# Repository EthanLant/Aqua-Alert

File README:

# Project Start: 01/12/26
# Contributors:
#   Finn Kramer
#   Ethan Lant
#   Braedyn Thompson
#   Damen Visscher
# Project:
#   Aqua Alert
# Contains:
#   Code for the Lifeguard System
#       - Information Processing, Water Sensor Compatability and Integration, Bluetooth Operation, Antenna Operation
#   Code for the Manager System
#       - Information Processing, LCD Operation and UI, Bluetooth Information Reception, Alert Operation (Yet to be Fully Determined)
#   Future PCB Design

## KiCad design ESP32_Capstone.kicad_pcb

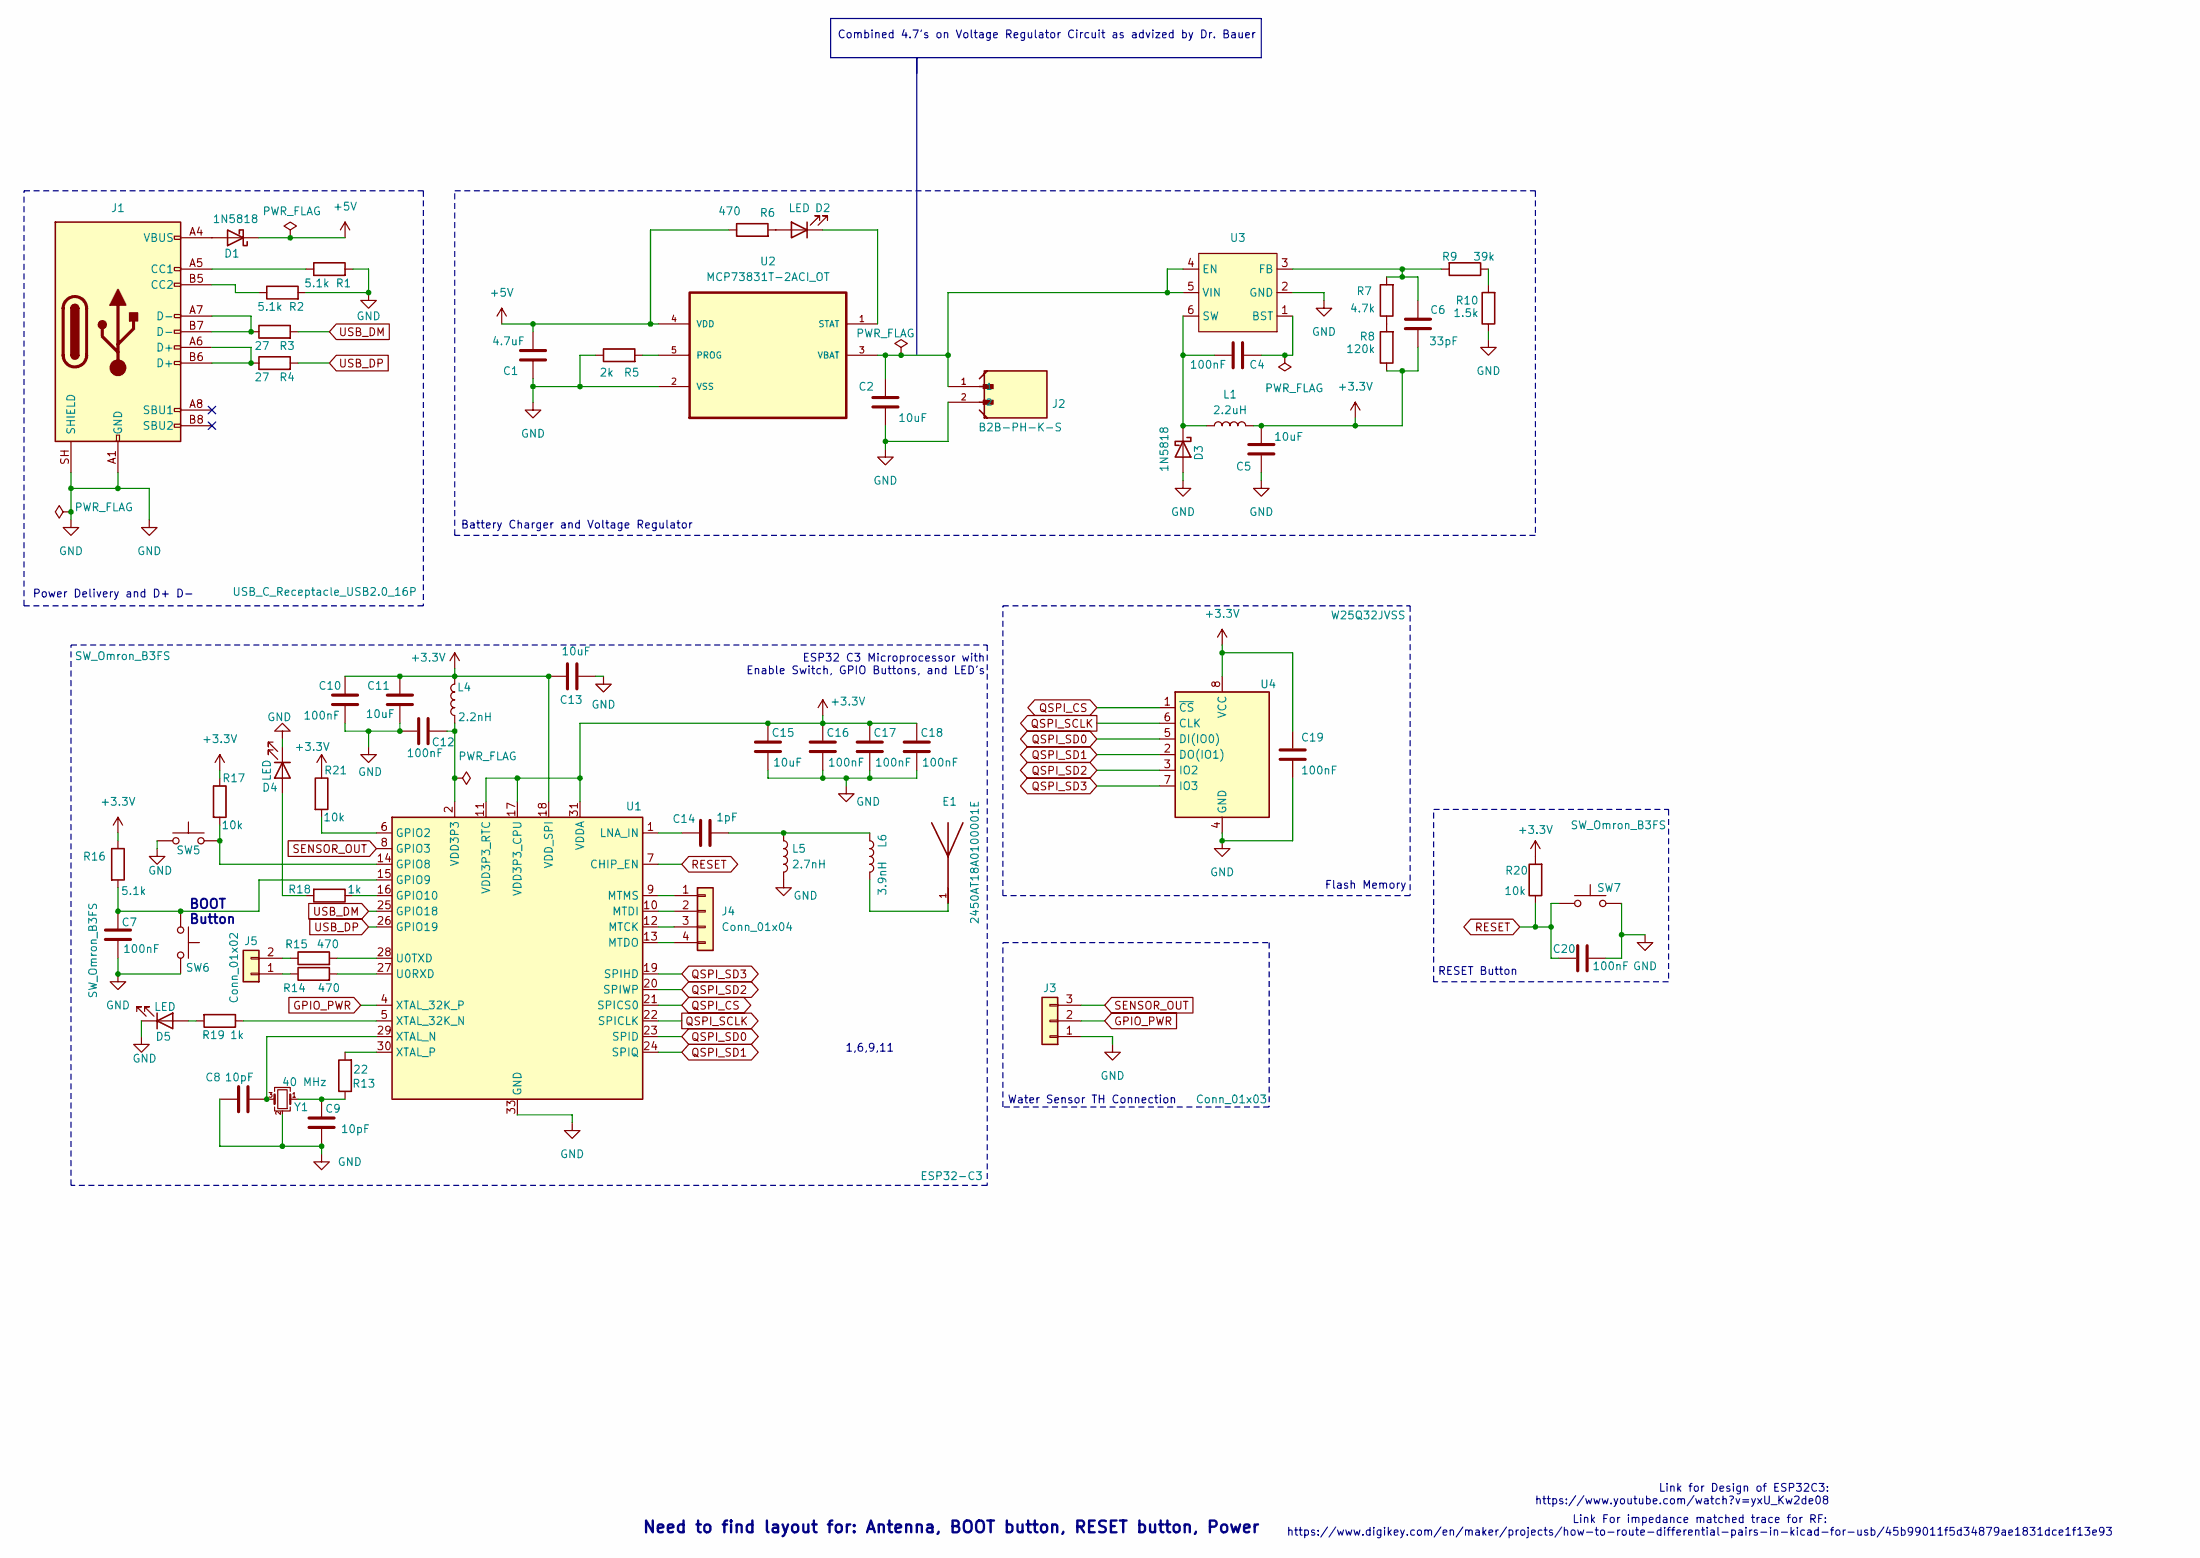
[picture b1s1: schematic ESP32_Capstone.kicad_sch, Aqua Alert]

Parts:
C1: 4.7uF; C_0805_2012Metric
C2, C5, C11, C13, C15: 10uF; C_0805_2012Metric
C4, C7, C10, C12, C16, C17, C18, C19, C20: 100nF; C_0805_2012Metric
C6: 33pF; C_0805_2012Metric
C8, C9: 10pF; C_0805_2012Metric
C14: 1pF; C_0603_1608Metric
D1, D3: 1N5818; D_SMA
D2, D4, D5: LED; LED_0805_2012Metric
E1: 2450AT18A0100001E; XCVR_2450AT18A0100001E; PARTREV 4.0
J1: USB_C_Receptacle_USB2.0_16P; USB_C_Receptacle_HRO_TYPE-C-31-M-12
J2: B2B-PH-K-S; JST_B2B-PH-K-S
J3: Conn_01x03; PinSocket_1x03_P2.54mm_Vertical
J4: Conn_01x04; PinSocket_1x04_P2.54mm_Vertical
J5: Conn_01x02; PinSocket_1x02_P2.54mm_Vertical
L1: 2.2uH; L_0805_2012Metric
L4: 2.2nH; L_0805_2012Metric
L5: 2.7nH; L_0603_1608Metric
L6: 3.9nH; L_0603_1608Metric
R1, R2, R16: 5.1k; R_0805_2012Metric
R3, R4: 27; R_0805_2012Metric
R5: 2k; R_0805_2012Metric
R6, R14, R15: 470; R_0805_2012Metric
R7: 4.7k; R_0603_1608Metric
R8: 120k; R_0603_1608Metric
R9: 39k; R_0603_1608Metric
R10: 1.5k; R_0603_1608Metric
R13: 22; R_0805_2012Metric
R17, R20, R21: 10k; R_0805_2012Metric
R18, R19: 1k; R_0805_2012Metric
SW5, SW6, SW7: SW_Omron_B3FS; SW_SPST_Omron_B3FS-100xP
U1: ESP32-C3; QFN50P500X500X90-33N
U2: MCP73831T-2ACI_OT; SOT95P280X145-5N; MPN MCP73831T-2ACI/OT
U3: SOT95P280X100-6N
U4: W25Q32JVSS; SOIC-8_5.23x5.23mm_P1.27mm
Y1: 40 MHz; Crystal_SMD_SeikoEpson_FA128-4Pin_2.0x1.6mm

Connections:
+5V: C1.1, D1.1 (K), R6.1, U2.4 (VDD)
GND: C1.2, C2.2, C5.2, C7.1, C8.2, C9.1, C10.1, C11.1, C12.1, C13.1, C15.1, C16.1, C17.1, C18.1, C19.2, C20.1, D3.2 (A), D4.1 (K), D5.1 (K), J1.A1 (GND), J1.A12 (GND), J1.B1 (GND), J1.B12 (GND), J1.SH (SHIELD), J2.2, J3.1, L5.2, R1.2, R2.2, R5.1, R10.1, SW5.1, SW6.2, SW7.2, U1.33 (GND), U2.2 (VSS), U3.2 (GND), U4.4 (GND), Y1.2 (G), Y1.4 (G)
GPIO_PWR: J3.2, U1.4 (XTAL_32K_P)
unnamed: C9.2, R13.1, Y1.1
unnamed: C12.2, L4.2, U1.2 (VDD3P3), U1.3 (VDD3P3)
unnamed: C14.1, L5.1, L6.1
unnamed: D1.2 (A), J1.A4 (VBUS), J1.A9 (VBUS), J1.B4 (VBUS), J1.B9 (VBUS)
unnamed: D2.2 (A), R6.2
unnamed: D2.1 (K), U2.1 (STAT)
unnamed: C4.1, D3.1 (K), L1.1, U3.6 (SW)
unnamed: D4.2 (A), R18.2
unnamed: D5.2 (A), R19.2
unnamed: E1.1, L6.2
unnamed: J1.A5 (CC1), R1.1
unnamed: J1.B5 (CC2), R2.1
unnamed: J1.A6 (D+), J1.B6 (D+), R4.1
unnamed: J1.A7 (D-), J1.B7 (D-), R3.1
unnamed: J4.1, U1.9 (MTMS)
unnamed: J4.2, U1.10 (MTDI)
unnamed: J4.3, U1.12 (MTCK)
unnamed: J4.4, U1.13 (MTDO)
unnamed: J5.1, R14.1
unnamed: J5.2, R15.1
unnamed: R7.1, R8.2
unnamed: R9.1, R10.2
unnamed: R21.2, U1.6 (GPIO2)
unnamed: R17.2, SW5.2, U1.14 (GPIO8)
unnamed: R18.1, U1.16 (GPIO10)
unnamed: C14.2, U1.1 (LNA_IN)
unnamed: R14.2, U1.27 (U0RXD)
unnamed: R15.2, U1.28 (U0TXD)
unnamed: R19.1, U1.5 (XTAL_32K_N)
unnamed: C8.1, U1.29 (XTAL_N), Y1.3
unnamed: R13.2, U1.30 (XTAL_P)
unnamed: R5.2, U2.5 (PROG)
unnamed: C2.1, J2.1, U2.3 (VBAT), U3.4 (EN), U3.5 (VIN)
unnamed: C4.2, U3.1 (BST)
unnamed: C6.1, R7.2, R9.2, U3.3 (FB)
QSPI_CS: U1.21 (SPICS0), U4.1 (~CS)
QSPI_SCLK: U1.22 (SPICLK), U4.6 (CLK)
QSPI_SD0: U1.23 (SPID), U4.5 (DI(IO0))
QSPI_SD1: U1.24 (SPIQ), U4.2 (DO(IO1))
QSPI_SD2: U1.20 (SPIWP), U4.3 (IO2)
QSPI_SD3: U1.19 (SPIHD), U4.7 (IO3)
RESET: C20.2, R20.1, SW7.1, U1.7 (CHIP_EN)
SENSOR_OUT: J3.3, U1.8 (GPIO3)
USB_DM: R3.2, U1.25 (GPIO18)
USB_DP: R4.2, U1.26 (GPIO19)

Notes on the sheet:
Water Sensor TH Connection
Flash Memory
Link For impedance matched trace for RF: https://www.digikey.com/en/maker/projects/how-to-route-differential-pairs-in-kicad-for-usb/45b99011f5d34879ae1831dce1f13e93
Need to find layout for: Antenna, BOOT button, RESET button, Power
Battery Charger and Voltage Regulator
Combined 4.7's on Voltage Regulator Circuit as advized by Dr. Bauer
Power Delivery and D+ D-
1,6,9,11
RESET Button
BOOT Button
ESP32 C3 Microprocessor with Enable Switch, GPIO Buttons, and LED's
Link for Design of ESP32C3: https://www.youtube.com/watch?v=yxU_Kw2de08

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
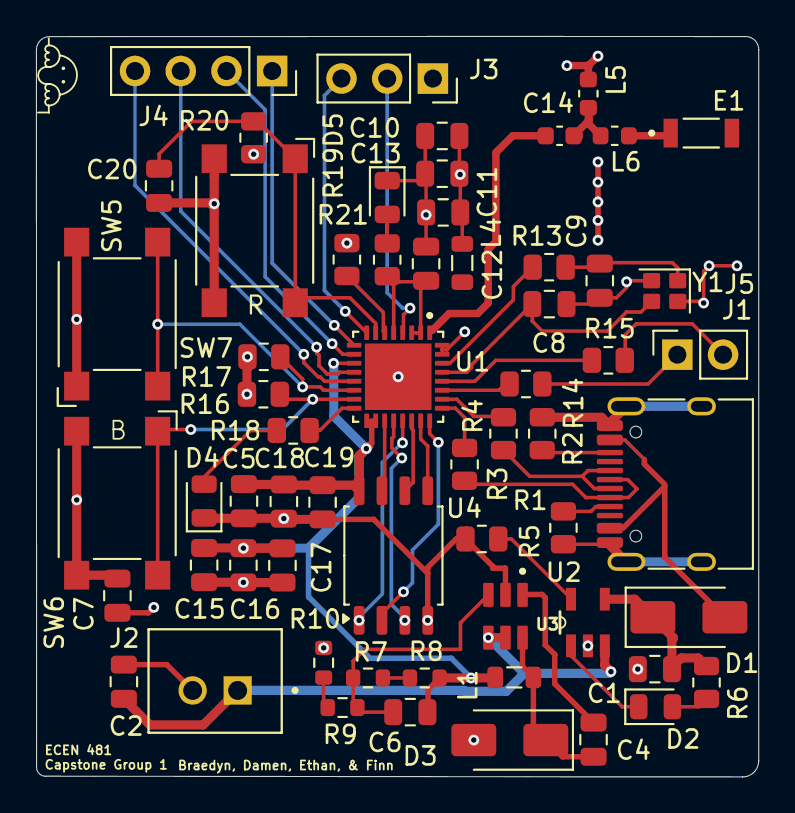
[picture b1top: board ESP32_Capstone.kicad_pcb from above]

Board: 4 copper layers, 40.1 x 41.1 mm, 61 parts (0 on the bottom side), 50 nets.

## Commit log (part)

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2026-02-07 README
2026-02-08 Create Test
2026-03-03 Currently Operating Server
    This file contains example code adapted to receive strings, display at terminal, and send signed int from {-10. 20}. This was made in collaboration with Finn, who has operating client code.
2026-03-26 Lifeguard PCB Schematic
    Most Recent iteration of the Schematic for the Lifeguard device, iteration by Ethan Lant
2026-03-31 Full Capstone Lifeguard PCB KiCAD project file
    Full project file upload to assist others in schematic updates.
2026-04-01 ESP32 Capstone PCB Schematic
    Most Recent iteration of PCB Schematic: 26-03-31
